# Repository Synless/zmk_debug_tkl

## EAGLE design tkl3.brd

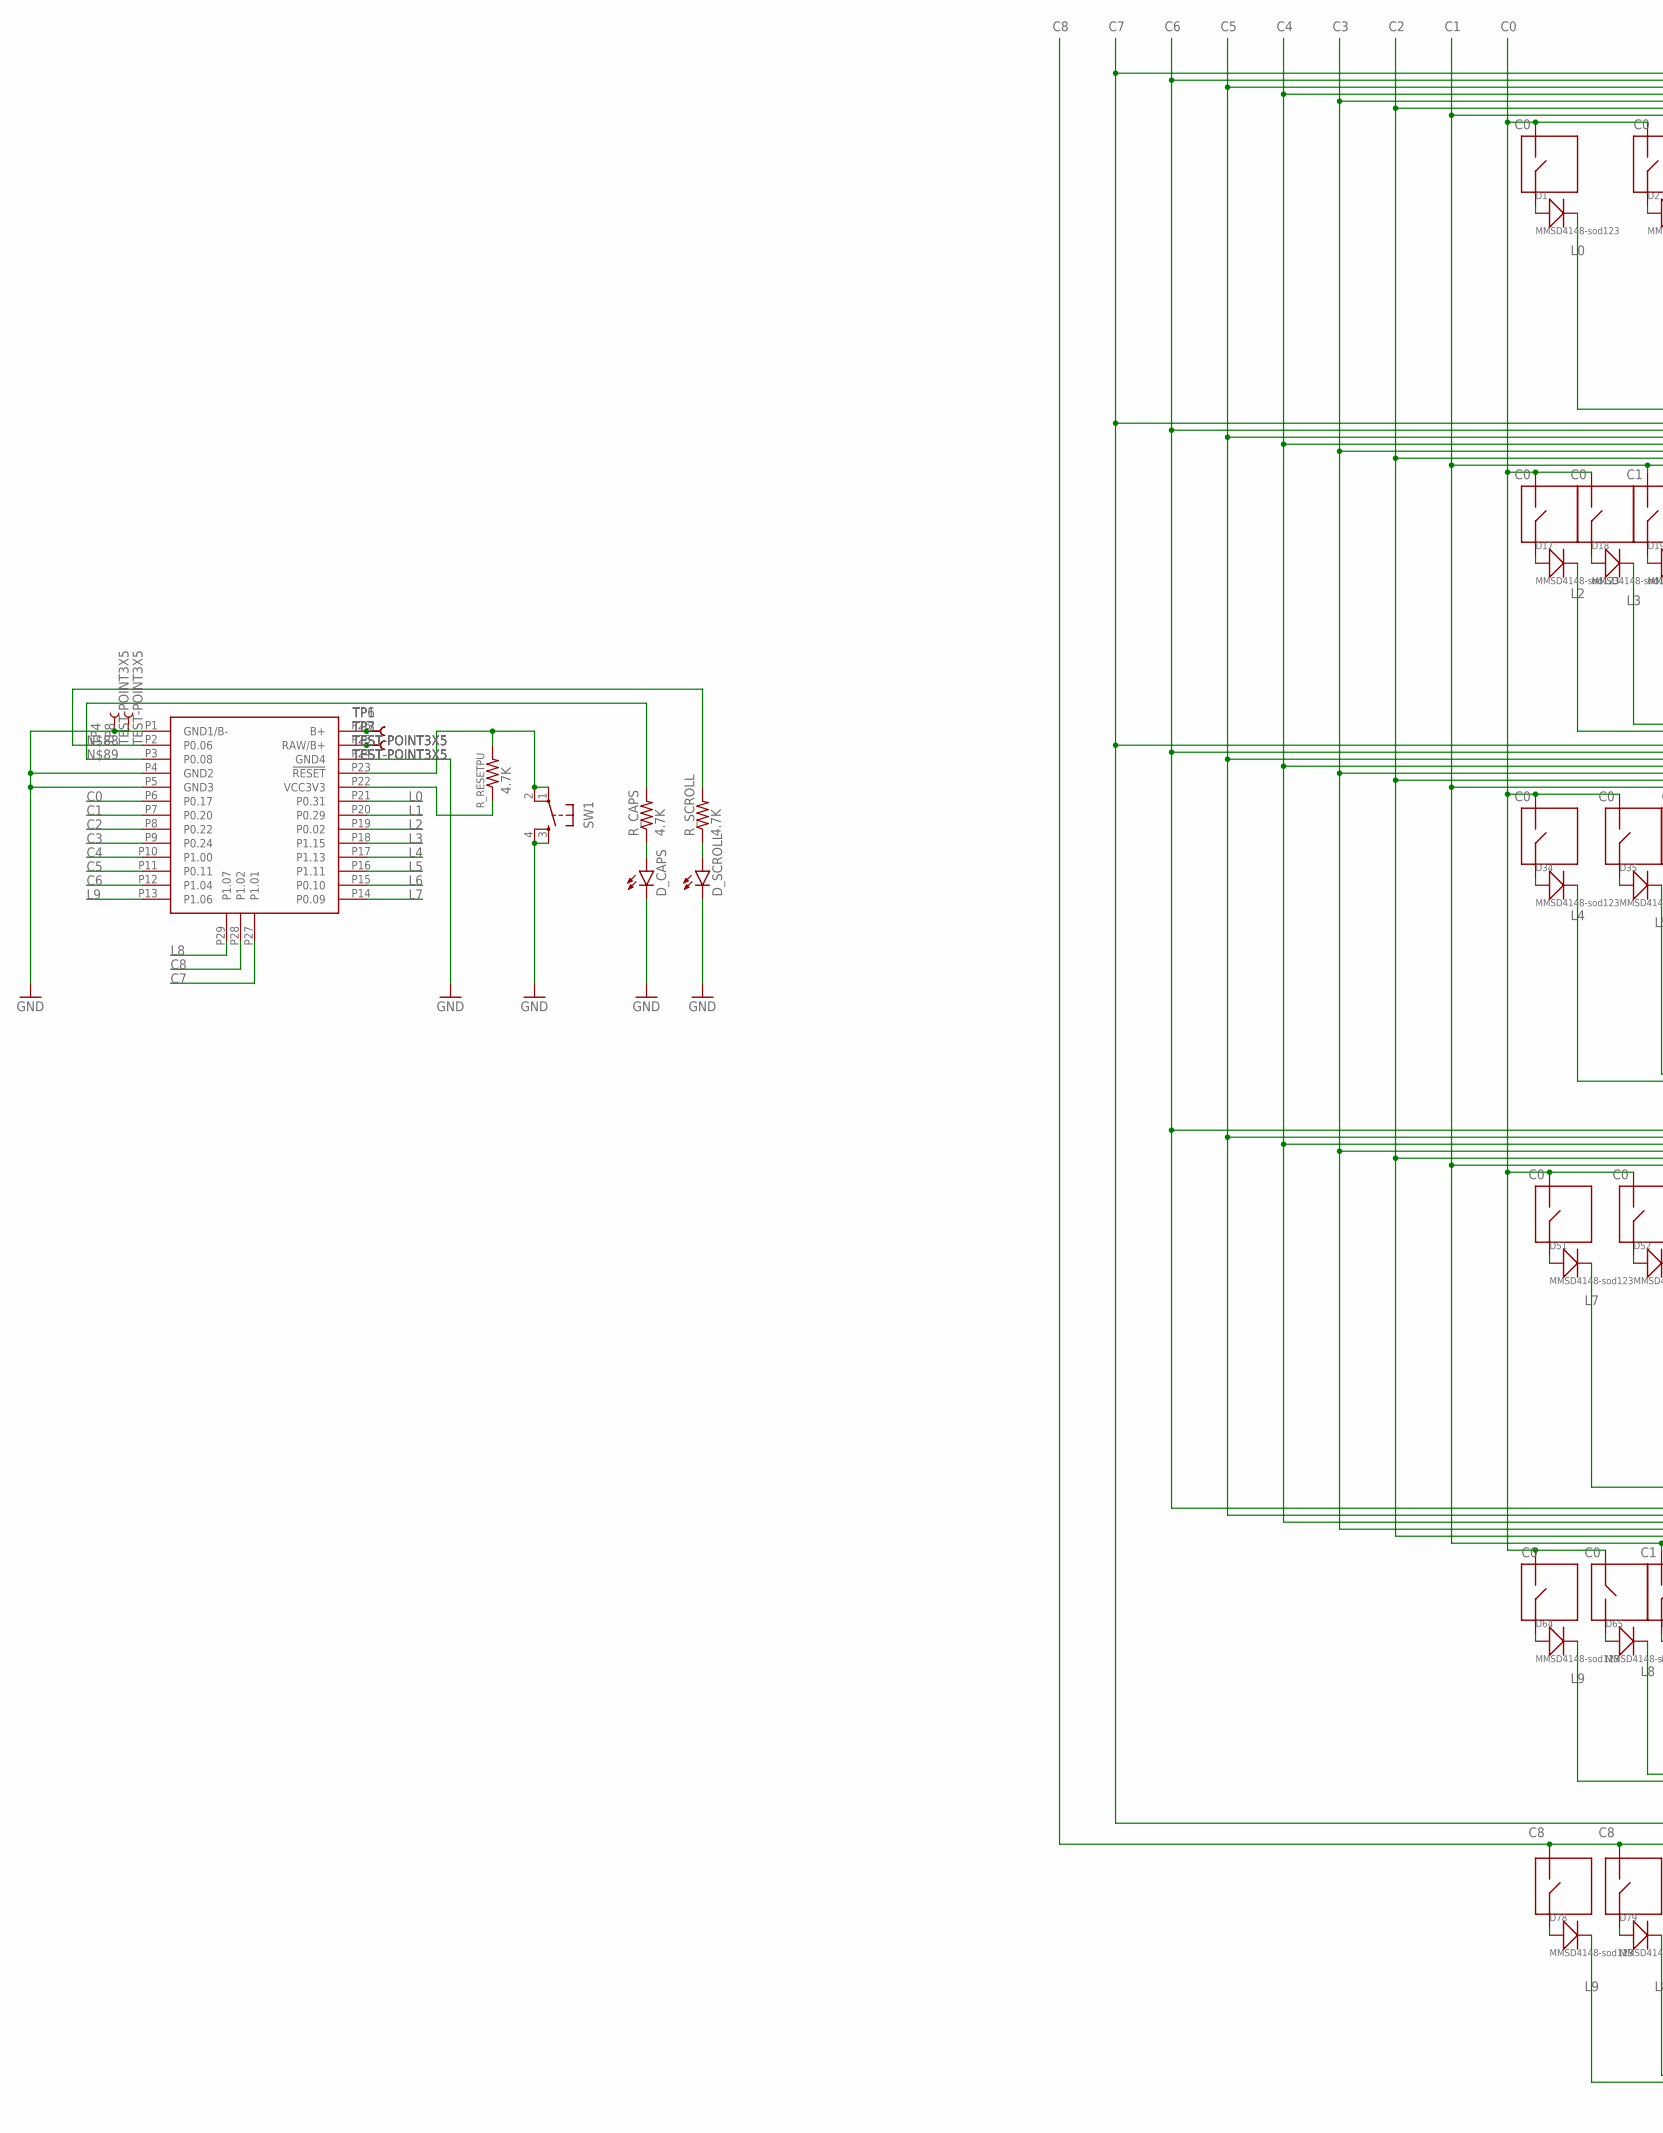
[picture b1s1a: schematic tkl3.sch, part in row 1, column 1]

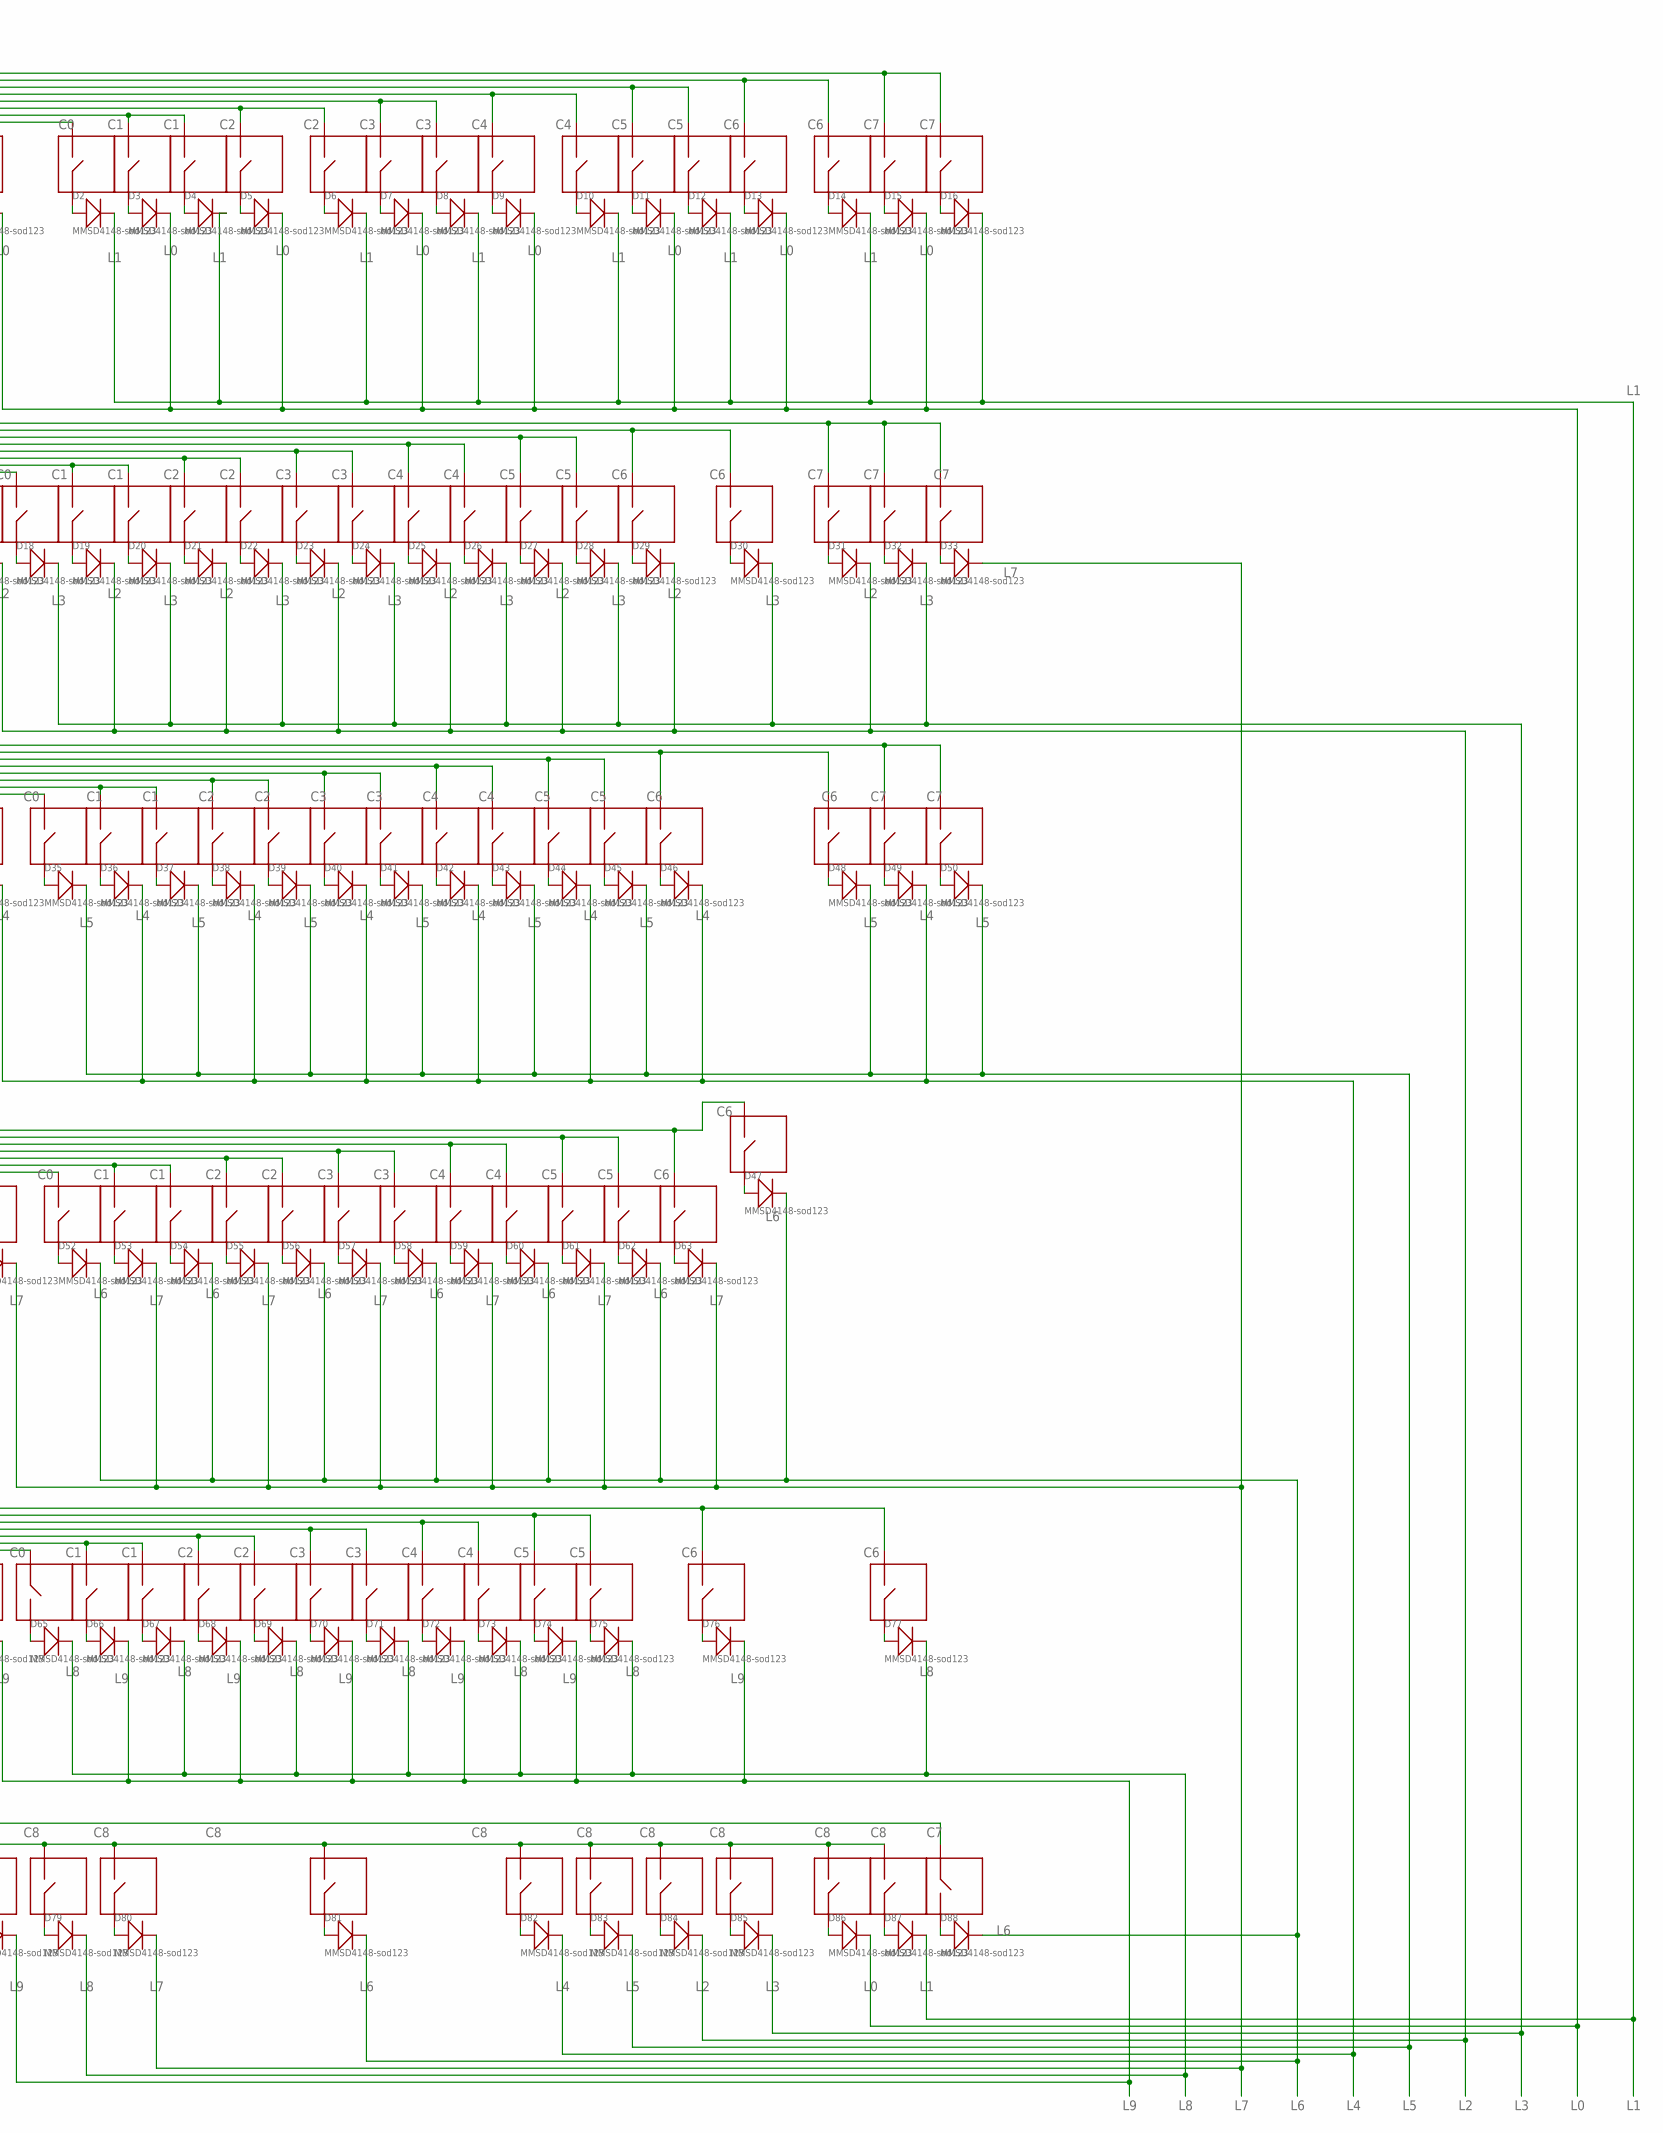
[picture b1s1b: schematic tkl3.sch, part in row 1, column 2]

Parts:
D1, D2, D3, D4, D5, D6, D7, D8, D9, D10, D11, D12, D13, D14, D15, D16, D17, D18, D19, D20, D21, D22, D23, D24, D25, D26, D27, D28, D29, D30, D31, D32, D33, D34, D35, D36, D37, D38, D39, D40, D41, D42, D43, D44, D45, D46, D47, D48, D49, D50, D51, D52, D53, D54, D55, D56, D57, D58, D59, D60, D61, D62, D63, D64, D65, D66, D67, D68, D69, D70, D71, D72, D73, D74, D75, D76, D77, D78, D79, D80, D81, D82, D83, D84, D85, D86, D87, D88: MMSD4148-sod123; SOD-123
D_CAPS: LED3MM
D_SCROLL: LED3MM
F_F2: CHERRY_MX1U; CHERRY_MX_NO_LED_SOCKET_1U
K_0, K_1, K_2, K_3, K_4, K_5, K_6, K_7, K_8, K_9: CHERRY_MX1U; CHERRY_MX_NO_LED_SOCKET_1U
K_A: CHERRY_MX1U; CHERRY_MX_NO_LED_SOCKET_1U
K_B: CHERRY_MX1U; CHERRY_MX_NO_LED_SOCKET_1U
K_BACK: CHERRY_MX1U; CHERRY_MX_NO_LED_SOCKET_1U
K_C: CHERRY_MX1U; CHERRY_MX_NO_LED_SOCKET_1U
K_CAPSLOCK: CHERRY_MX1U; CHERRY_MX_NO_LED_SOCKET_1U
K_COMA: CHERRY_MX1U; CHERRY_MX_NO_LED_SOCKET_1U
K_D: CHERRY_MX1U; CHERRY_MX_NO_LED_SOCKET_1U
K_DELETE: CHERRY_MX1U; CHERRY_MX_NO_LED_SOCKET_1U
K_DOT: CHERRY_MX1U; CHERRY_MX_NO_LED_SOCKET_1U
K_DOWN: CHERRY_MX1U; CHERRY_MX_NO_LED_SOCKET_1U
K_E: CHERRY_MX1U; CHERRY_MX_NO_LED_SOCKET_1U
K_ECH: CHERRY_MX1U; CHERRY_MX_NO_LED_SOCKET_1U
K_END: CHERRY_MX1U; CHERRY_MX_NO_LED_SOCKET_1U
K_ENTER: CHERRY_MX1U; CHERRY_MX_NO_LED_SOCKET_1U
K_F, K_F1, K_F3, K_F4, K_F5, K_F6, K_F7, K_F8, K_F9, K_F10, K_F11, K_F12: CHERRY_MX1U; CHERRY_MX_NO_LED_SOCKET_1U
K_FN: CHERRY_MX1U; CHERRY_MX_NO_LED_SOCKET_1U
K_G: CHERRY_MX1U; CHERRY_MX_NO_LED_SOCKET_1U
K_H: CHERRY_MX1U; CHERRY_MX_NO_LED_SOCKET_1U
K_HOME: CHERRY_MX1U; CHERRY_MX_NO_LED_SOCKET_1U
K_I: CHERRY_MX1U; CHERRY_MX_NO_LED_SOCKET_1U
K_INSERT: CHERRY_MX1U; CHERRY_MX_NO_LED_SOCKET_1U
K_J: CHERRY_MX1U; CHERRY_MX_NO_LED_SOCKET_1U
K_K: CHERRY_MX1U; CHERRY_MX_NO_LED_SOCKET_1U
K_L: CHERRY_MX1U; CHERRY_MX_NO_LED_SOCKET_1U
K_LALT: CHERRY_MX1U; CHERRY_MX_NO_LED_SOCKET_1U
K_LBRA: CHERRY_MX1U; CHERRY_MX_NO_LED_SOCKET_1U
K_LCTRL: CHERRY_MX1U; CHERRY_MX_NO_LED_SOCKET_1U
K_LEFT: CHERRY_MX1U; CHERRY_MX_NO_LED_SOCKET_1U
K_LSHFT: CHERRY_MX1U; CHERRY_MX_NO_LED_SOCKET_1U
K_LWIN: CHERRY_MX1U; CHERRY_MX_NO_LED_SOCKET_1U
K_M: CHERRY_MX1U; CHERRY_MX_NO_LED_SOCKET_1U
K_MINUS: CHERRY_MX1U; CHERRY_MX_NO_LED_SOCKET_1U
K_N: CHERRY_MX1U; CHERRY_MX_NO_LED_SOCKET_1U
K_O: CHERRY_MX1U; CHERRY_MX_NO_LED_SOCKET_1U
K_P: CHERRY_MX1U; CHERRY_MX_NO_LED_SOCKET_1U
K_PAUSE: CHERRY_MX1U; CHERRY_MX_NO_LED_SOCKET_1U
K_PDW: CHERRY_MX1U; CHERRY_MX_NO_LED_SOCKET_1U
K_PIPE: CHERRY_MX1U; CHERRY_MX_NO_LED_SOCKET_1U
K_PLUS: CHERRY_MX1U; CHERRY_MX_NO_LED_SOCKET_1U
K_PRNT: CHERRY_MX1U; CHERRY_MX_NO_LED_SOCKET_1U
K_PUP: CHERRY_MX1U; CHERRY_MX_NO_LED_SOCKET_1U
K_Q: CHERRY_MX1U; CHERRY_MX_NO_LED_SOCKET_1U
K_QUOTE: CHERRY_MX1U; CHERRY_MX_NO_LED_SOCKET_1U
K_R: CHERRY_MX1U; CHERRY_MX_NO_LED_SOCKET_1U
K_RALT: CHERRY_MX1U; CHERRY_MX_NO_LED_SOCKET_1U
K_RBRA: CHERRY_MX1U; CHERRY_MX_NO_LED_SOCKET_1U
K_RCTRL: CHERRY_MX1U; CHERRY_MX_NO_LED_SOCKET_1U
K_RIGHT: CHERRY_MX1U; CHERRY_MX_NO_LED_SOCKET_1U
K_RSHFT: CHERRY_MX1U; CHERRY_MX_NO_LED_SOCKET_1U
K_RWIN: CHERRY_MX1U; CHERRY_MX_NO_LED_SOCKET_1U
K_S: CHERRY_MX1U; CHERRY_MX_NO_LED_SOCKET_1U
K_SCROL: CHERRY_MX1U; CHERRY_MX_NO_LED_SOCKET_1U
K_SEMIC: CHERRY_MX1U; CHERRY_MX_NO_LED_SOCKET_1U
K_SLASH: CHERRY_MX1U; CHERRY_MX_NO_LED_SOCKET_1U
K_SPACE: CHERRY_MX1U; CHERRY_MX_NO_LED_SOCKET_1U
K_T: CHERRY_MX1U; CHERRY_MX_NO_LED_SOCKET_1U
K_TAB: CHERRY_MX1U; CHERRY_MX_NO_LED_SOCKET_1U
K_U: CHERRY_MX1U; CHERRY_MX_NO_LED_SOCKET_1U
K_UP: CHERRY_MX1U; CHERRY_MX_NO_LED_SOCKET_1U
K_V: CHERRY_MX1U; CHERRY_MX_NO_LED_SOCKET_1U
K_W: CHERRY_MX1U; CHERRY_MX_NO_LED_SOCKET_1U
K_WAVE: CHERRY_MX1U; CHERRY_MX_NO_LED_SOCKET_1U
K_X: CHERRY_MX1U; CHERRY_MX_NO_LED_SOCKET_1U
K_Y: CHERRY_MX1U; CHERRY_MX_NO_LED_SOCKET_1U
K_Z: CHERRY_MX1U; CHERRY_MX_NO_LED_SOCKET_1U
R_CAPS: 4.7K; 0603-RES
R_RESETPU: 4.7K; 0603-RES
R_SCROLL: 4.7K; 0603-RES
SW1: SWITCH_SPST_4_PINRECT; TACTILE_SWITCH_SMD_4.6X2.8MM
TP1, TP3, TP4, TP6, TP7, TP8: TEST-POINT3X5; PAD.03X.05
U$1: NICE_NANO
Κ_GRV: CHERRY_MX1U; CHERRY_MX_NO_LED_SOCKET_1U

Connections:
C0: K_1.PIN2, K_A.PIN2, K_CAPSLOCK.PIN2, K_ECH.PIN2, K_F1.PIN2, K_LSHFT.PIN2, K_PIPE.PIN1, K_Q.PIN2, K_TAB.PIN2, U$1.P6 (P0.17), Κ_GRV.PIN2
C1: F_F2.PIN2, K_2.PIN2, K_3.PIN2, K_D.PIN2, K_E.PIN2, K_F3.PIN2, K_S.PIN2, K_W.PIN2, K_X.PIN2, K_Z.PIN2, U$1.P7 (P0.20)
C2: K_4.PIN2, K_5.PIN2, K_C.PIN2, K_F.PIN2, K_F4.PIN2, K_F5.PIN2, K_G.PIN2, K_R.PIN2, K_T.PIN2, K_V.PIN2, U$1.P8 (P0.22)
C3: K_6.PIN2, K_7.PIN2, K_B.PIN2, K_F6.PIN2, K_F7.PIN2, K_H.PIN2, K_J.PIN2, K_N.PIN2, K_U.PIN2, K_Y.PIN2, U$1.P9 (P0.24)
C4: K_8.PIN2, K_9.PIN2, K_COMA.PIN2, K_F8.PIN2, K_F9.PIN2, K_I.PIN2, K_K.PIN2, K_L.PIN2, K_M.PIN2, K_O.PIN2, U$1.P10 (P1.00)
C5: K_0.PIN2, K_DOT.PIN2, K_F10.PIN2, K_F11.PIN2, K_LBRA.PIN2, K_MINUS.PIN2, K_P.PIN2, K_QUOTE.PIN2, K_SEMIC.PIN2, K_SLASH.PIN2, U$1.P11 (P0.11)
C6: K_BACK.PIN2, K_DELETE.PIN2, K_ENTER.PIN2, K_F12.PIN2, K_PLUS.PIN2, K_PRNT.PIN2, K_RBRA.PIN2, K_RSHFT.PIN2, K_UP.PIN2, K_WAVE.PIN2, U$1.P12 (P1.04)
C7: K_END.PIN2, K_HOME.PIN2, K_INSERT.PIN2, K_PAUSE.PIN2, K_PDW.PIN2, K_PUP.PIN2, K_RIGHT.PIN1, K_SCROL.PIN2, U$1.P27 (P1.01)
C8: K_DOWN.PIN2, K_FN.PIN2, K_LALT.PIN2, K_LCTRL.PIN2, K_LEFT.PIN2, K_LWIN.PIN2, K_RALT.PIN2, K_RCTRL.PIN2, K_RWIN.PIN2, K_SPACE.PIN2, U$1.P28 (P1.02)
GND: D_CAPS.K (C), D_SCROLL.K (C), SW1.3, SW1.4, TP4.P$1, TP8.P$1, U$1.P1 (GND1/B-), U$1.P4 (GND2), U$1.P5 (GND3), U$1.P24 (GND4)
L0: D1.-, D3.-, D5.-, D7.-, D9.-, D11.-, D13.-, D15.-, D86.-, U$1.P21 (P0.31)
L1: D2.-, D4.-, D6.-, D8.-, D10.-, D12.-, D14.-, D16.-, D87.-, U$1.P20 (P0.29)
L2: D17.-, D19.-, D21.-, D23.-, D25.-, D27.-, D29.-, D31.-, D84.-, U$1.P19 (P0.02)
L3: D18.-, D20.-, D22.-, D24.-, D26.-, D28.-, D30.-, D32.-, D85.-, U$1.P18 (P1.15)
L4: D34.-, D36.-, D38.-, D40.-, D42.-, D44.-, D46.-, D49.-, D82.-, U$1.P17 (P1.13)
L5: D35.-, D37.-, D39.-, D41.-, D43.-, D45.-, D48.-, D50.-, D83.-, U$1.P16 (P1.11)
L6: D47.-, D52.-, D54.-, D56.-, D58.-, D60.-, D62.-, D81.-, D88.-, U$1.P15 (P0.10)
L7: D33.-, D51.-, D53.-, D55.-, D57.-, D59.-, D61.-, D63.-, D80.-, U$1.P14 (P0.09)
L8: D65.-, D67.-, D69.-, D71.-, D73.-, D75.-, D77.-, D79.-, U$1.P29 (P1.07)
L9: D64.-, D66.-, D68.-, D70.-, D72.-, D74.-, D76.-, D78.-, U$1.P13 (P1.06)
unnamed: D88.+, K_RIGHT.PIN2
unnamed: D1.+, K_ECH.PIN1
unnamed: D2.+, K_F1.PIN1
unnamed: D3.+, F_F2.PIN1
unnamed: D4.+, K_F3.PIN1
unnamed: D5.+, K_F4.PIN1
unnamed: D6.+, K_F5.PIN1
unnamed: D7.+, K_F6.PIN1
unnamed: D8.+, K_F7.PIN1
unnamed: D9.+, K_F8.PIN1
unnamed: D10.+, K_F9.PIN1
unnamed: D11.+, K_F10.PIN1
unnamed: D12.+, K_F11.PIN1
unnamed: D13.+, K_F12.PIN1
unnamed: D14.+, K_PRNT.PIN1
unnamed: D15.+, K_SCROL.PIN1
unnamed: D16.+, K_PAUSE.PIN1
unnamed: D33.+, K_PUP.PIN1
unnamed: D32.+, K_HOME.PIN1
unnamed: D31.+, K_INSERT.PIN1
unnamed: D30.+, K_BACK.PIN1
unnamed: D29.+, K_PLUS.PIN1
unnamed: D28.+, K_MINUS.PIN1
unnamed: D27.+, K_0.PIN1
unnamed: D26.+, K_9.PIN1
unnamed: D25.+, K_8.PIN1
unnamed: D24.+, K_7.PIN1
unnamed: D23.+, K_6.PIN1
unnamed: D22.+, K_5.PIN1
unnamed: D21.+, K_4.PIN1
unnamed: D20.+, K_3.PIN1
unnamed: D19.+, K_2.PIN1
unnamed: D18.+, K_1.PIN1
unnamed: D17.+, Κ_GRV.PIN1
unnamed: D34.+, K_TAB.PIN1
unnamed: D35.+, K_Q.PIN1
unnamed: D36.+, K_W.PIN1
unnamed: D37.+, K_E.PIN1
unnamed: D38.+, K_R.PIN1
unnamed: D39.+, K_T.PIN1
unnamed: D40.+, K_Y.PIN1
unnamed: D41.+, K_U.PIN1
unnamed: D42.+, K_I.PIN1
unnamed: D43.+, K_O.PIN1
unnamed: D44.+, K_P.PIN1
unnamed: D45.+, K_LBRA.PIN1
unnamed: D46.+, K_RBRA.PIN1
unnamed: D47.+, K_ENTER.PIN1
unnamed: D48.+, K_DELETE.PIN1
unnamed: D49.+, K_END.PIN1
unnamed: D50.+, K_PDW.PIN1
unnamed: D51.+, K_CAPSLOCK.PIN1
unnamed: D52.+, K_A.PIN1
unnamed: D53.+, K_S.PIN1
unnamed: D54.+, K_D.PIN1
unnamed: D55.+, K_F.PIN1
unnamed: D56.+, K_G.PIN1
unnamed: D57.+, K_H.PIN1
unnamed: D58.+, K_J.PIN1
unnamed: D59.+, K_K.PIN1
unnamed: D60.+, K_L.PIN1
unnamed: D61.+, K_SEMIC.PIN1
unnamed: D62.+, K_QUOTE.PIN1
unnamed: D63.+, K_WAVE.PIN1
unnamed: D64.+, K_LSHFT.PIN1
unnamed: D65.+, K_PIPE.PIN2
unnamed: D66.+, K_Z.PIN1
unnamed: D67.+, K_X.PIN1
unnamed: D68.+, K_C.PIN1
unnamed: D69.+, K_V.PIN1
unnamed: D70.+, K_B.PIN1
unnamed: D71.+, K_N.PIN1
unnamed: D72.+, K_M.PIN1
unnamed: D73.+, K_COMA.PIN1
unnamed: D74.+, K_DOT.PIN1
unnamed: D75.+, K_SLASH.PIN1
unnamed: D76.+, K_RSHFT.PIN1
unnamed: D77.+, K_UP.PIN1
unnamed: D78.+, K_LCTRL.PIN1
unnamed: D79.+, K_LWIN.PIN1
unnamed: D82.+, K_RALT.PIN1
unnamed: D81.+, K_SPACE.PIN1
unnamed: D83.+, K_RWIN.PIN1
unnamed: D84.+, K_RCTRL.PIN1
unnamed: D85.+, K_FN.PIN1
unnamed: D86.+, K_LEFT.PIN1
unnamed: D87.+, K_DOWN.PIN1
unnamed: R_CAPS.2, U$1.P3 (P0.08)
unnamed: R_SCROLL.2, U$1.P2 (P0.06)
unnamed: D_CAPS.A, R_CAPS.1
unnamed: D_SCROLL.A, R_SCROLL.1
unnamed: R_RESETPU.2, SW1.1, SW1.2, U$1.P23 (!RESET)
unnamed: R_RESETPU.1, U$1.P22 (VCC3V3)
unnamed: TP1.P$1, TP6.P$1, U$1.P26 (B+)
unnamed: TP3.P$1, TP7.P$1, U$1.P25 (RAW/B+)
unnamed: D80.+, K_LALT.PIN1

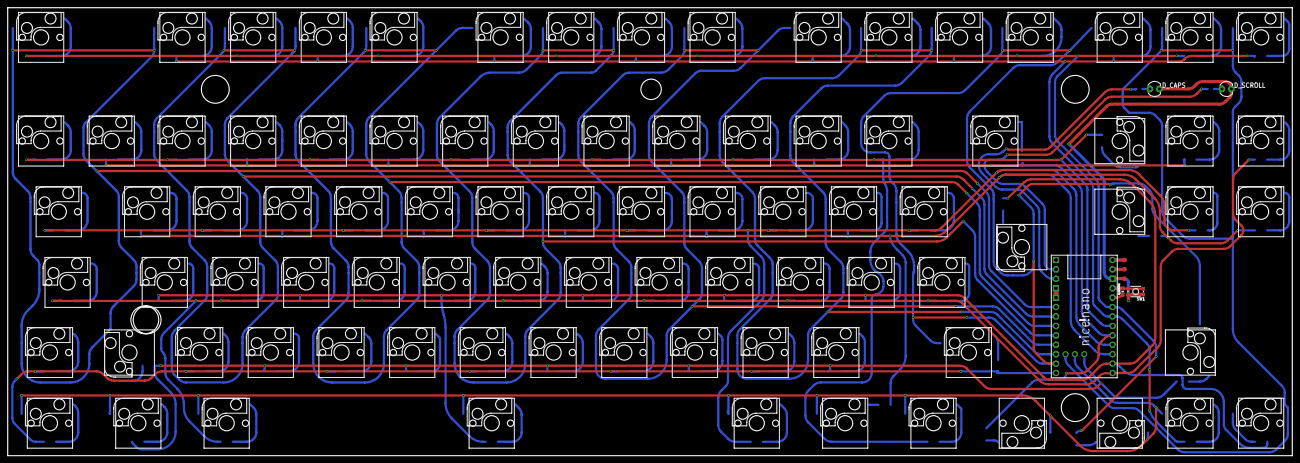
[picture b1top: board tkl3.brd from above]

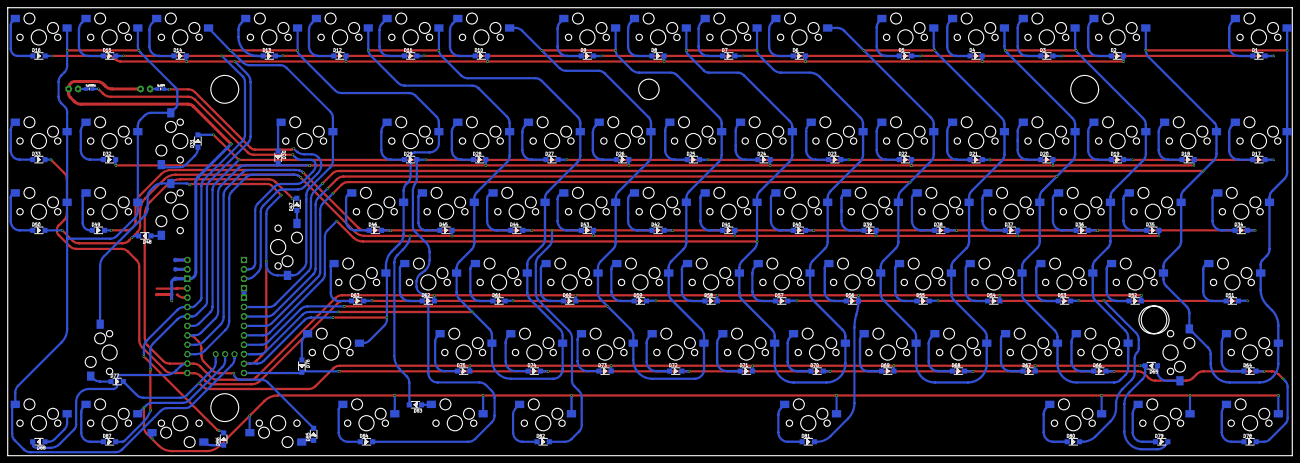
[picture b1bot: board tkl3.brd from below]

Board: 2 copper layers, 346.2 x 120.7 mm, 189 parts (93 on the bottom side), 116 nets.

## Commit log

2023-01-09 working config

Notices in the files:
parts and their libraries:
SparkFun-LED: Licensing: Creative Commons ShareAlike 4.0 International - https://creativecommons.org/licenses/by-sa/4.0
